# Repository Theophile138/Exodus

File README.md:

# Exodus

## Documentation

[Documentation du code](./Software/Doc)

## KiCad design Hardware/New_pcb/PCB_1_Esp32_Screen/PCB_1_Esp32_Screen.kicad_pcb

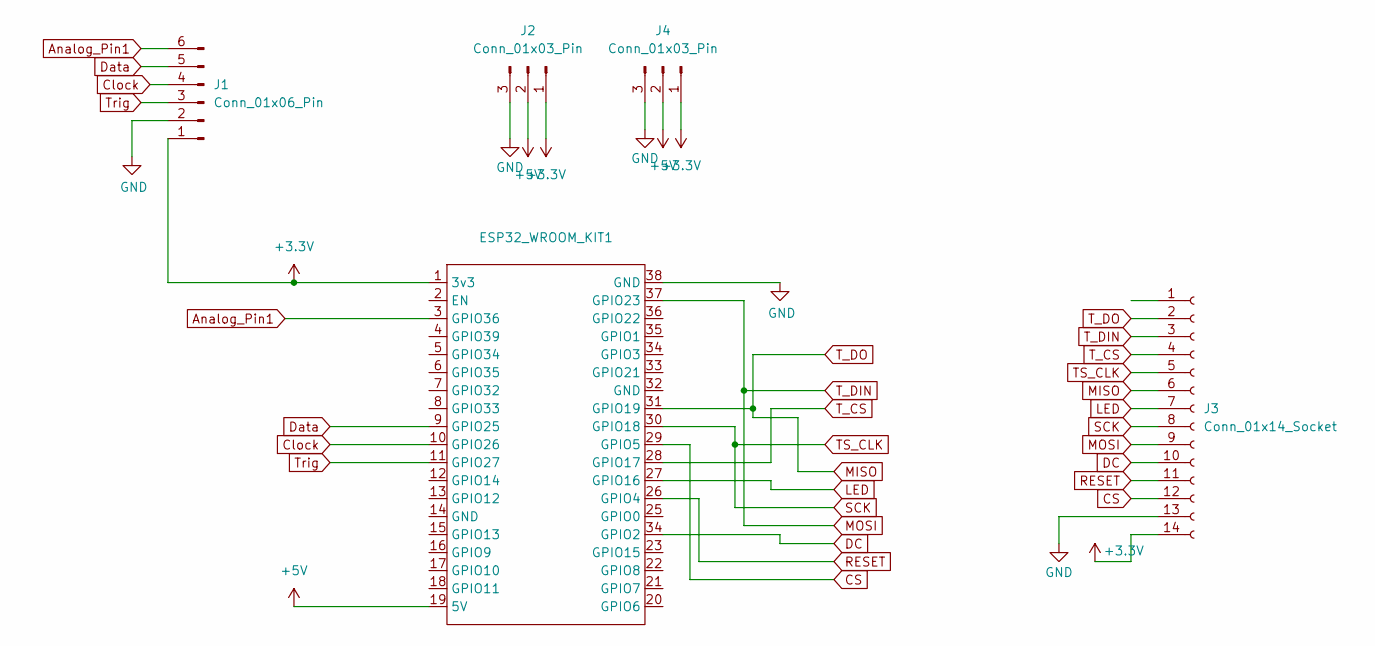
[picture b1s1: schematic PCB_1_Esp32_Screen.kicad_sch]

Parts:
ESP32_WROOM_KIT1: Esp32_Wroom32_DevKit
J1: Conn_01x06_Pin; PinHeader_1x06_P2.54mm_Vertical
J2, J4: Conn_01x03_Pin; PinHeader_1x03_P2.54mm_Vertical
J3: Conn_01x14_Socket; PinSocket_1x14_P2.54mm_Vertical

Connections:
+3.3V: ESP32_WROOM_KIT1.1 (3v3), J1.1, J2.1, J3.14, J4.1
+5V: ESP32_WROOM_KIT1.19 (5V), J2.2, J4.2
Analog_Pin1: ESP32_WROOM_KIT1.3 (GPIO36), J1.6
CS: ESP32_WROOM_KIT1.29 (GPIO5), J3.12
Clock: ESP32_WROOM_KIT1.10 (GPIO26), J1.4
DC: ESP32_WROOM_KIT1.34 (GPIO2), J3.10
Data: ESP32_WROOM_KIT1.9 (GPIO25), J1.5
GND: ESP32_WROOM_KIT1.38 (GND), J1.2, J2.3, J3.13, J4.3
LED: ESP32_WROOM_KIT1.27 (GPIO16), J3.7
MISO: ESP32_WROOM_KIT1.31 (GPIO19), J3.2, J3.6
MOSI: ESP32_WROOM_KIT1.37 (GPIO23), J3.3, J3.9
RESET: ESP32_WROOM_KIT1.26 (GPIO4), J3.11
SCK: ESP32_WROOM_KIT1.30 (GPIO18), J3.5, J3.8
T_CS: ESP32_WROOM_KIT1.28 (GPIO17), J3.4
Trig: ESP32_WROOM_KIT1.11 (GPIO27), J1.3

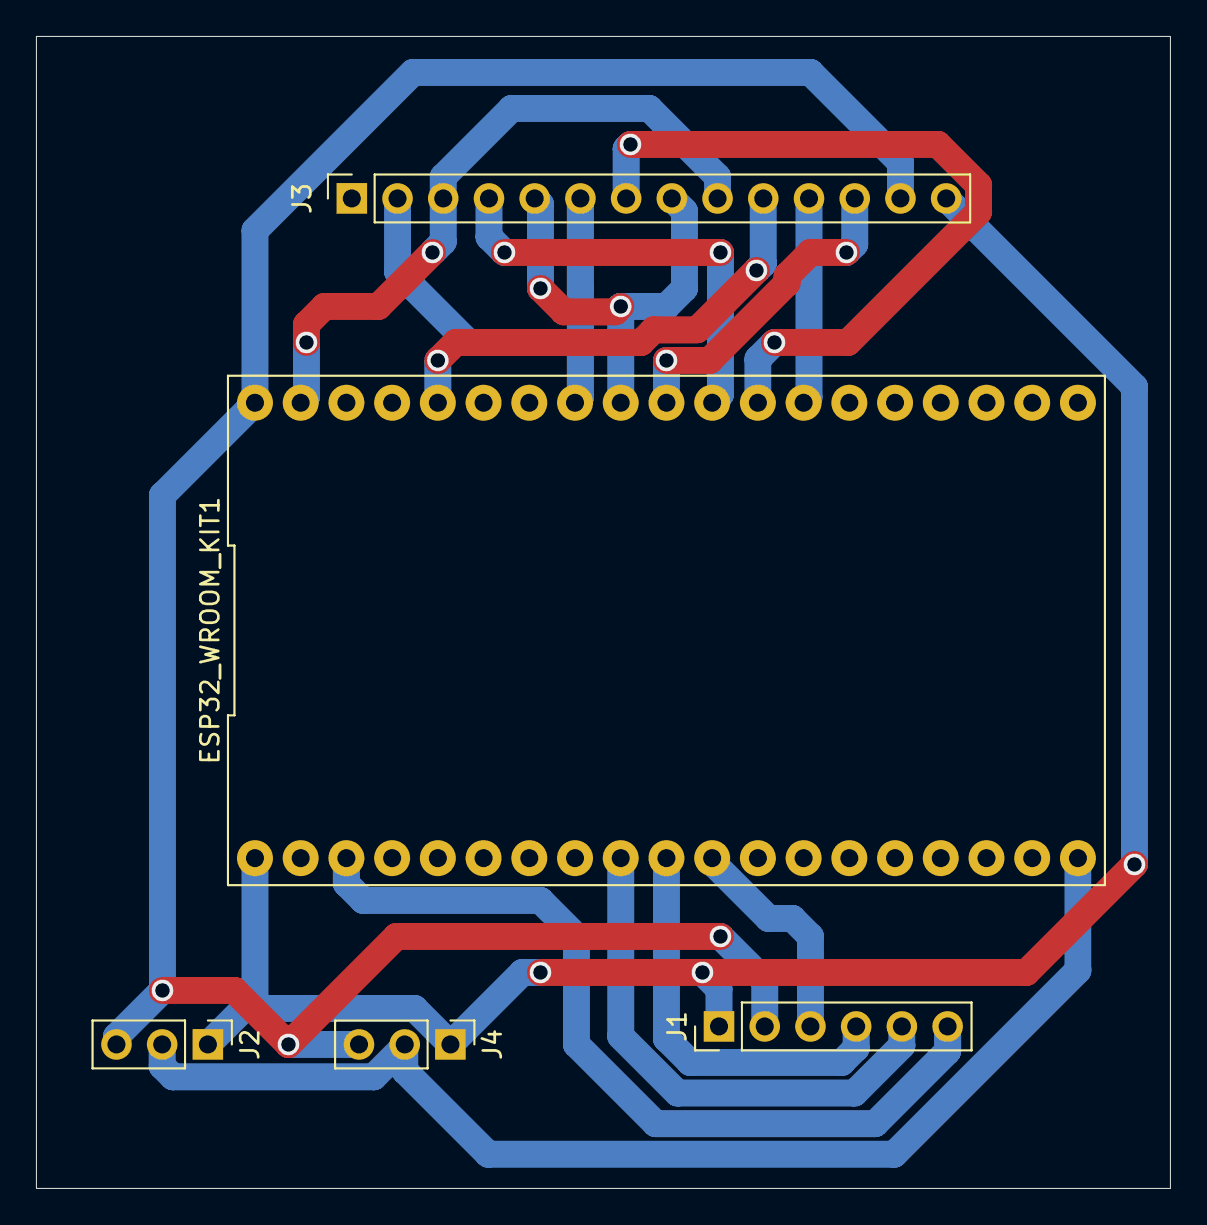
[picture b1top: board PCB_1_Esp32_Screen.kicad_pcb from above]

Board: 2 copper layers, 63.0 x 64.0 mm, 5 parts (0 on the bottom side), 15 nets.

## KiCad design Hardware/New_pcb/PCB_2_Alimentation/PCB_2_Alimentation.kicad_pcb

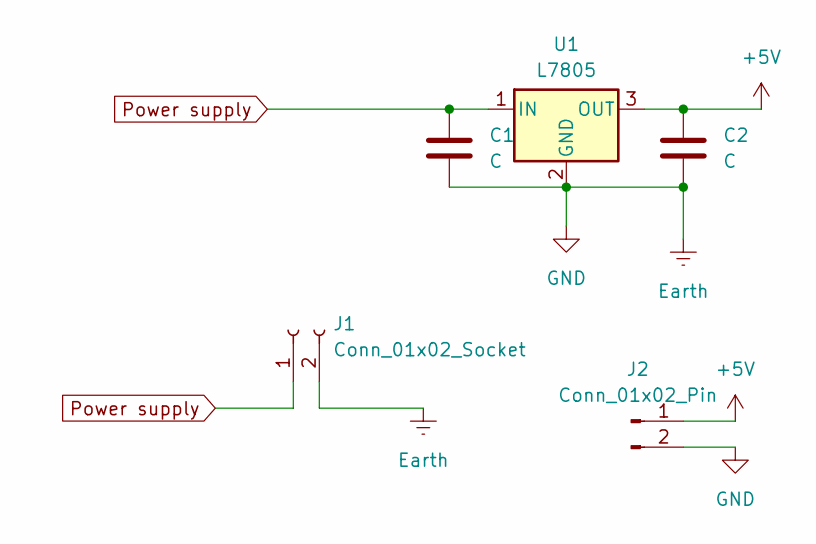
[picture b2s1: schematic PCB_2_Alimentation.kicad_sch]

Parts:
C1, C2: C; CP_Radial_D4.0mm_P1.50mm
J1: Conn_01x02_Socket; TerminalBlock_bornier-2_P5.08mm
J2: Conn_01x02_Pin; PinHeader_1x02_P2.54mm_Horizontal
U1: L7805; TO-220-3_Vertical

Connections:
+5V: C2.1, J2.1, U1.3 (OUT)
Earth: C1.2, C2.2, J1.2, J2.2, U1.2 (GND)
Power supply: C1.1, J1.1, U1.1 (IN)

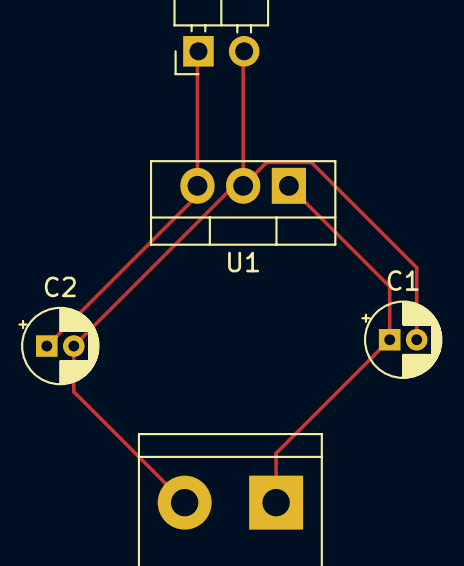
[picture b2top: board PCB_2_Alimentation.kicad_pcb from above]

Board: 2 copper layers, 5 parts (0 on the bottom side), 3 nets.

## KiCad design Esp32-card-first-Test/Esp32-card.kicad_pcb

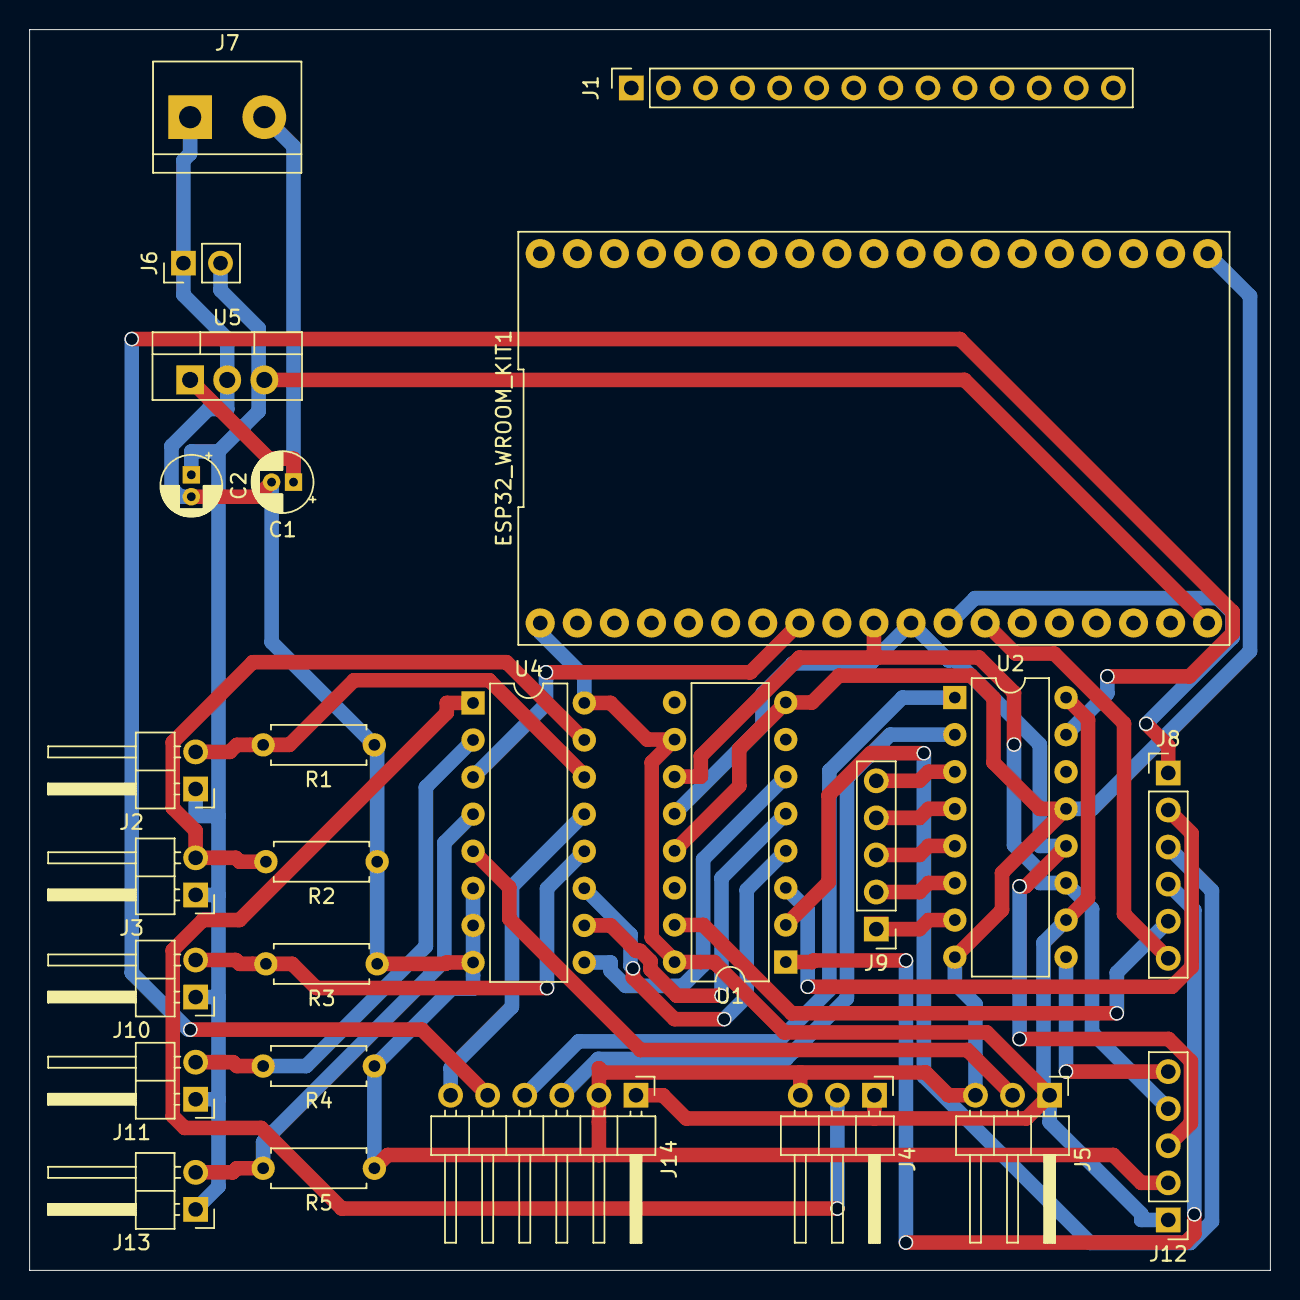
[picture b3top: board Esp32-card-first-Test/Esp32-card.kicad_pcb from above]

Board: 2 copper layers, 85.0 x 85.0 mm, 26 parts (0 on the bottom side), 35 nets.

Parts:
C1, C2: C; CP_Radial_D4.0mm_P1.50mm
ESP32_WROOM_KIT1: Esp32_Wroom32_DevKit
J1: Conn_01x14_Socket; PinSocket_1x14_P2.54mm_Vertical
J2, J3, J10, J11, J13: Conn_01x02_Pin; PinHeader_1x02_P2.54mm_Horizontal
J4, J5: Conn_01x03_Pin; PinHeader_1x03_P2.54mm_Horizontal
J6: Conn_01x02_Pin; PinHeader_1x02_P2.54mm_Vertical
J7: Conn_01x02_Socket; TerminalBlock_bornier-2_P5.08mm
J8: Conn_01x06_Pin; PinHeader_1x06_P2.54mm_Vertical
J9, J12: Conn_01x05_Pin; PinHeader_1x05_P2.54mm_Vertical
J14: Conn_01x06_Pin; PinHeader_1x06_P2.54mm_Horizontal
R1, R2, R3, R4, R5: R; R_Axial_DIN0207_L6.3mm_D2.5mm_P7.62mm_Horizontal
U1, U2: 74HC595; DIP-16_W7.62mm
U4: 74HC4051; DIP-16_W7.62mm
U5: L7805; TO-220-3_Vertical

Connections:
3v3: ESP32_WROOM_KIT1.1 (3v3), J4.1, J5.1, J12.1, J14.1, U1.10 (~SRCLR), U1.16 (VCC), U2.10 (~SRCLR), U2.16 (VCC), U4.16 (VCC)
5v: C2.1, ESP32_WROOM_KIT1.19 (5V), J2.1, J3.1, J6.2, J10.1, J11.1, J13.1, U5.3 (OUT)
Analog_Pin1: ESP32_WROOM_KIT1.8 (GPIO33), U4.3 (A)
Capteur_Autre_1: J11.2, R4.2, U4.2 (A6)
Capteur_Autre_2: J13.2, R5.2, U4.4 (A7)
Capteur_Force_1: J2.2, R1.2, U4.14 (A1)
Capteur_Force_2: J3.2, R2.2, U4.15 (A2)
Capteur_Force_3: J10.2, R3.2, U4.12 (A3)
Capteur_Hall_1: J4.2, U4.1 (A4)
Capteur_Hall_2: J5.2, U4.5 (A5)
Clock: ESP32_WROOM_KIT1.10 (GPIO26), J12.4, U1.11 (SRCLK), U2.11 (SRCLK)
Data: ESP32_WROOM_KIT1.9 (GPIO25), U1.14 (SER)
GND: C1.2, C2.2, ESP32_WROOM_KIT1.20 (GND), J4.3, J5.3, J6.1, J7.1, J12.2, J14.2, R1.1, R2.1, R3.1, R4.1, R5.1, U1.8 (GND), U1.13 (~OE), U2.8 (GND), U2.13 (~OE), U4.6 (~E), U4.7 (VEE), U4.8 (GND), U5.2 (GND)
M1_Pin_Dir1: J8.5, U1.15 (QA)
M1_Pin_Dir2: J8.4, U1.1 (QB)
M1_Pin_EN: ESP32_WROOM_KIT1.13 (GPIO12), J8.6
M2_Pin_Dir1: J8.3, U1.2 (QC)
M2_Pin_Dir2: J8.2, U1.3 (QD)
M2_Pin_EN: ESP32_WROOM_KIT1.12 (GPIO14), J8.1
unnamed: J9.1, U2.7 (QH)
unnamed: J9.2, U2.6 (QG)
unnamed: J9.3, U2.5 (QF)
unnamed: J9.4, U2.4 (QE)
unnamed: J9.5, U2.3 (QD)
unnamed: J12.5, U2.9 (QH')
unnamed: J14.3, U2.2 (QC)
unnamed: J14.4, U2.1 (QB)
unnamed: J14.5, U2.15 (QA)
unnamed: J14.6, U4.13 (A0)
unnamed: U1.4 (QE), U4.11 (S0)
unnamed: U1.5 (QF), U4.10 (S1)
unnamed: U1.6 (QG), U4.9 (S2)
unnamed: U1.9 (QH'), U2.14 (SER)
Power supply: C1.1, J7.2, U5.1 (IN)
Trig: ESP32_WROOM_KIT1.11 (GPIO27), J12.3, U1.12 (RCLK), U2.12 (RCLK)

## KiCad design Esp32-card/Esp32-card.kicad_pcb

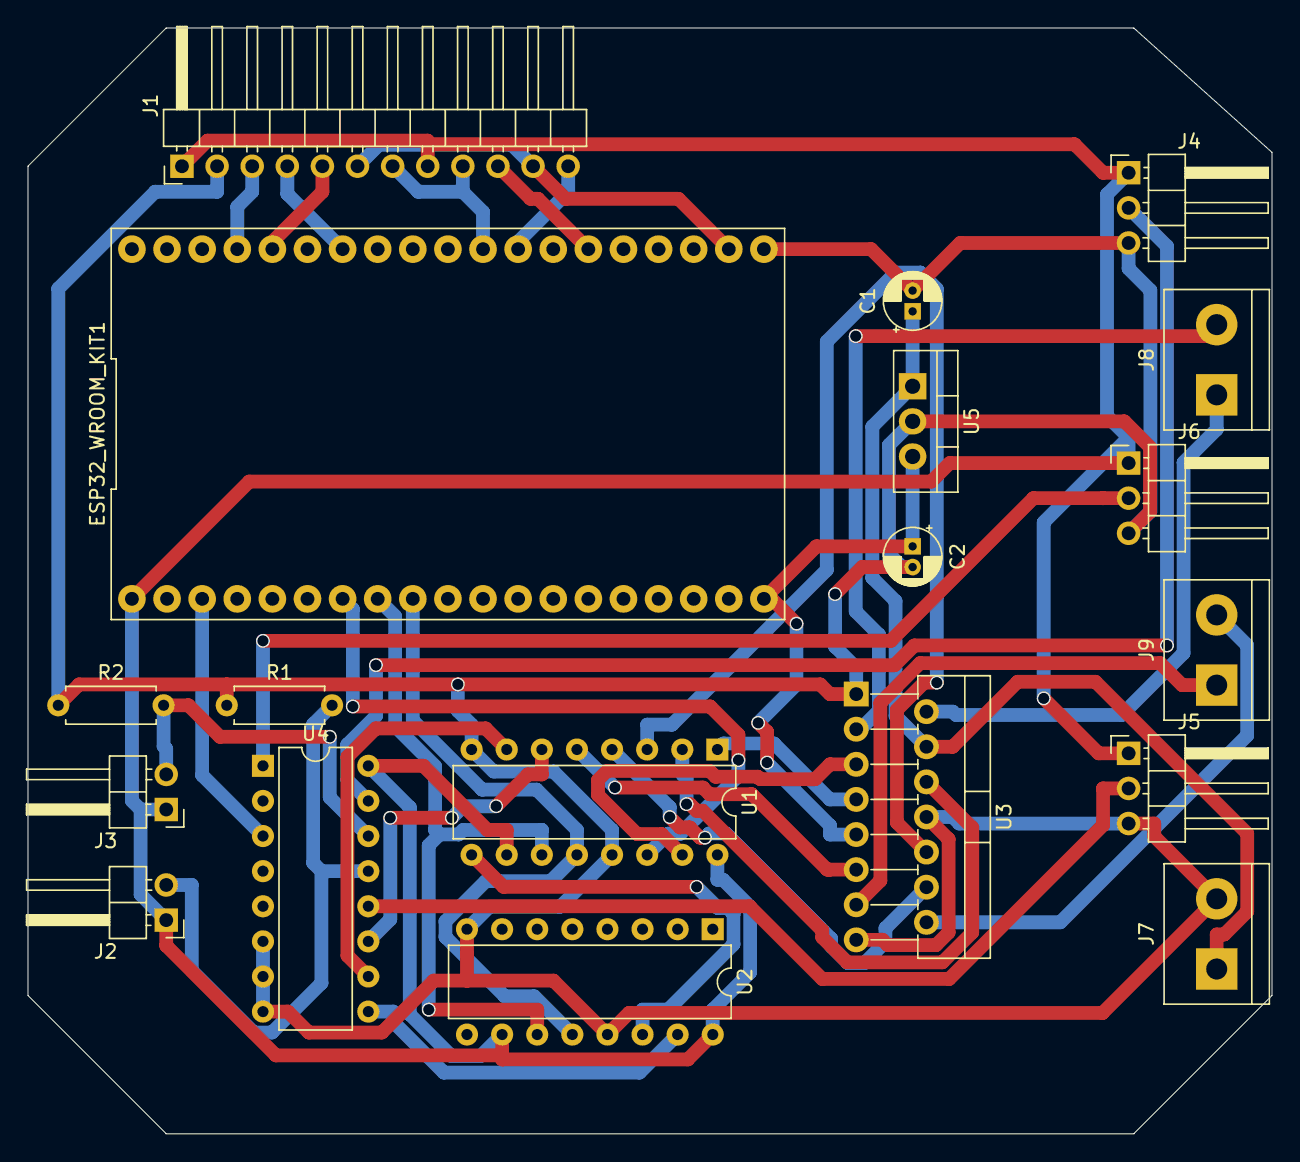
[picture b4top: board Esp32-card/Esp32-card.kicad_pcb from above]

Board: 2 copper layers, 90.0 x 80.0 mm, 19 parts (0 on the bottom side), 34 nets.

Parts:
C1, C2: C; CP_Radial_D4.0mm_P1.50mm
ESP32_WROOM_KIT1: Esp32_Wroom32_DevKit
J1: Conn_01x12_Pin; PinHeader_1x12_P2.54mm_Horizontal
J2, J3: Conn_01x02_Pin; PinHeader_1x02_P2.54mm_Horizontal
J4, J5, J6: Conn_01x03_Pin; PinHeader_1x03_P2.54mm_Horizontal
J7, J8, J9: Conn_01x02_Socket; TerminalBlock_bornier-2_P5.08mm
R1, R2: R; R_Axial_DIN0207_L6.3mm_D2.5mm_P7.62mm_Horizontal
U1, U2: 74HC595; DIP-16_W7.62mm
U3: L298N; TO-220-15_P2.54x2.54mm_StaggerOdd_Lead4.58mm_Vertical
U4: 74HC4051; DIP-16_W7.62mm
U5: L7805; TO-220-3_Vertical

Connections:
3v3: ESP32_WROOM_KIT1.1 (3v3), J1.1, J1.8, J2.1, J3.1, J4.1, J5.1, J6.1, U1.10 (~SRCLR), U1.16 (VCC), U2.10 (~SRCLR), U2.16 (VCC), U4.16 (VCC)
5v: C2.1, ESP32_WROOM_KIT1.19 (5V), U3.9 (Vss), U5.3 (OUT)
Analog_Pin1: ESP32_WROOM_KIT1.3 (GPIO36), U4.3 (A)
Capteur_Flexion_1: J2.2, R1.2, U4.13 (A0)
Capteur_Flexion_2: J3.2, R2.2, U4.14 (A1)
Capteur_Hall_1: J4.2, U4.15 (A2)
Capteur_Hall_2: J5.2, U4.12 (A3)
Capteur_Hall_3: J6.2, U4.1 (A4)
Clock: ESP32_WROOM_KIT1.8 (GPIO33), U1.11 (SRCLK), U2.11 (SRCLK)
Data: ESP32_WROOM_KIT1.7 (GPIO32), U1.14 (SER)
GND: C1.2, C2.2, ESP32_WROOM_KIT1.20 (GND), J1.2, J4.3, J5.3, J6.3, J7.2, R1.1, R2.1, U1.8 (GND), U1.13 (~OE), U2.8 (GND), U2.13 (~OE), U3.1 (SENSE_A), U3.8 (GND), U3.15 (SENSE_B), U4.6 (~E), U4.7 (VEE), U4.8 (GND), U5.2 (GND)
M1_Pin_Dir1: U1.15 (QA), U3.5 (IN1)
M1_Pin_Dir2: U1.1 (QB), U3.7 (IN2)
M1_Pin_EN: U1.2 (QC), U3.6 (EnA)
M2_Pin_Dir1: U1.3 (QD), U3.10 (IN3)
M2_Pin_Dir2: U1.4 (QE), U3.12 (IN4)
M2_Pin_EN: U1.5 (QF), U3.11 (EnB)
unnamed: ESP32_WROOM_KIT1.34 (GPIO2), J1.5
unnamed: ESP32_WROOM_KIT1.32 (GPIO4), J1.4
unnamed: ESP32_WROOM_KIT1.35 (GPIO15), J1.3
unnamed: ESP32_WROOM_KIT1.28 (GPIO18), J1.7, J1.9
unnamed: ESP32_WROOM_KIT1.27 (GPIO19), J1.12
unnamed: ESP32_WROOM_KIT1.25 (GPIO21), J1.10
unnamed: ESP32_WROOM_KIT1.21 (GPIO23), J1.6, J1.11
unnamed: J8.1, U3.2 (OUT1)
unnamed: J8.2, U3.3 (OUT2)
unnamed: J9.1, U3.13 (OUT3)
unnamed: J9.2, U3.14 (OUT4)
unnamed: U1.6 (QG), U4.11 (S0)
unnamed: U1.9 (QH'), U2.14 (SER)
unnamed: U1.7 (QH), U4.10 (S1)
unnamed: U2.15 (QA), U4.9 (S2)
Power supply: C1.1, J7.1, U3.4 (Vs), U5.1 (IN)
Trig: ESP32_WROOM_KIT1.9 (GPIO25), U1.12 (RCLK), U2.12 (RCLK)

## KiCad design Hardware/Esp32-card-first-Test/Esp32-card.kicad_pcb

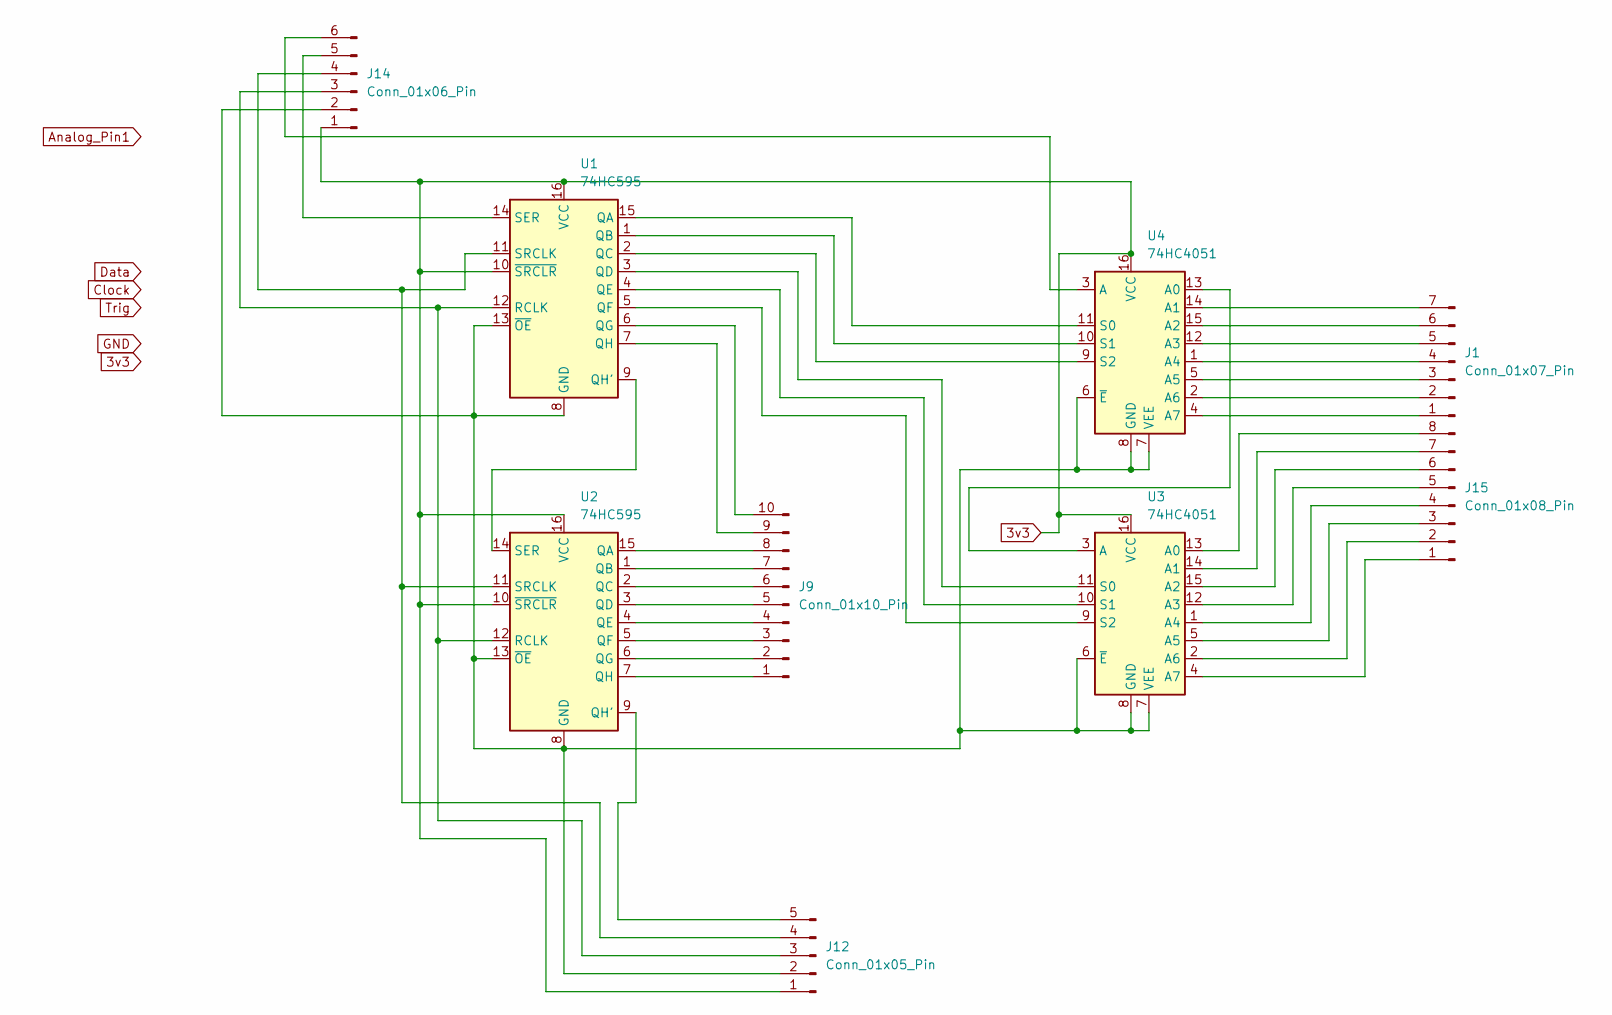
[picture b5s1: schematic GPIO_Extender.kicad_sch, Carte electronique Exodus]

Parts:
J1: Conn_01x07_Pin; PinHeader_1x07_P2.54mm_Vertical
J9: Conn_01x10_Pin; PinHeader_1x10_P2.54mm_Vertical
J12: Conn_01x05_Pin; PinHeader_1x05_P2.54mm_Vertical
J14: Conn_01x06_Pin; PinHeader_1x06_P2.54mm_Vertical
J15: Conn_01x08_Pin; PinHeader_1x08_P2.54mm_Vertical
U1, U2: 74HC595; DIP-16_W7.62mm
U3, U4: 74HC4051; DIP-16_W7.62mm

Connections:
3v3: J12.1, J14.1, U1.10 (~SRCLR), U1.16 (VCC), U2.10 (~SRCLR), U2.16 (VCC), U3.16 (VCC), U4.16 (VCC)
unnamed: J1.1, U4.4 (A7)
unnamed: J1.2, U4.2 (A6)
unnamed: J1.3, U4.5 (A5)
unnamed: J1.4, U4.1 (A4)
unnamed: J1.5, U4.12 (A3)
unnamed: J1.6, U4.15 (A2)
unnamed: J1.7, U4.14 (A1)
unnamed: J9.1, U2.7 (QH)
unnamed: J9.2, U2.6 (QG)
unnamed: J9.3, U2.5 (QF)
unnamed: J9.4, U2.4 (QE)
unnamed: J9.5, U2.3 (QD)
unnamed: J9.6, U2.2 (QC)
unnamed: J9.7, U2.1 (QB)
unnamed: J9.8, U2.15 (QA)
unnamed: J9.9, U1.7 (QH)
unnamed: J9.10, U1.6 (QG)
unnamed: J12.2, J14.2, U1.8 (GND), U1.13 (~OE), U2.8 (GND), U2.13 (~OE), U3.6 (~E), U3.7 (VEE), U3.8 (GND), U4.6 (~E), U4.7 (VEE), U4.8 (GND)
unnamed: J12.3, J14.3, U1.12 (RCLK), U2.12 (RCLK)
unnamed: J12.4, J14.4, U1.11 (SRCLK), U2.11 (SRCLK)
unnamed: J12.5, U2.9 (QH')
unnamed: J14.5, U1.14 (SER)
unnamed: J14.6, U4.3 (A)
unnamed: J15.1, U3.4 (A7)
unnamed: J15.2, U3.2 (A6)
unnamed: J15.3, U3.5 (A5)
unnamed: J15.4, U3.1 (A4)
unnamed: J15.5, U3.12 (A3)
unnamed: J15.6, U3.15 (A2)
unnamed: J15.7, U3.14 (A1)
unnamed: J15.8, U3.13 (A0)
unnamed: U1.15 (QA), U4.11 (S0)
unnamed: U1.1 (QB), U4.10 (S1)
unnamed: U1.2 (QC), U4.9 (S2)
unnamed: U1.3 (QD), U3.11 (S0)
unnamed: U1.4 (QE), U3.10 (S1)
unnamed: U1.5 (QF), U3.9 (S2)
unnamed: U1.9 (QH'), U2.14 (SER)
unnamed: U3.3 (A), U4.13 (A0)

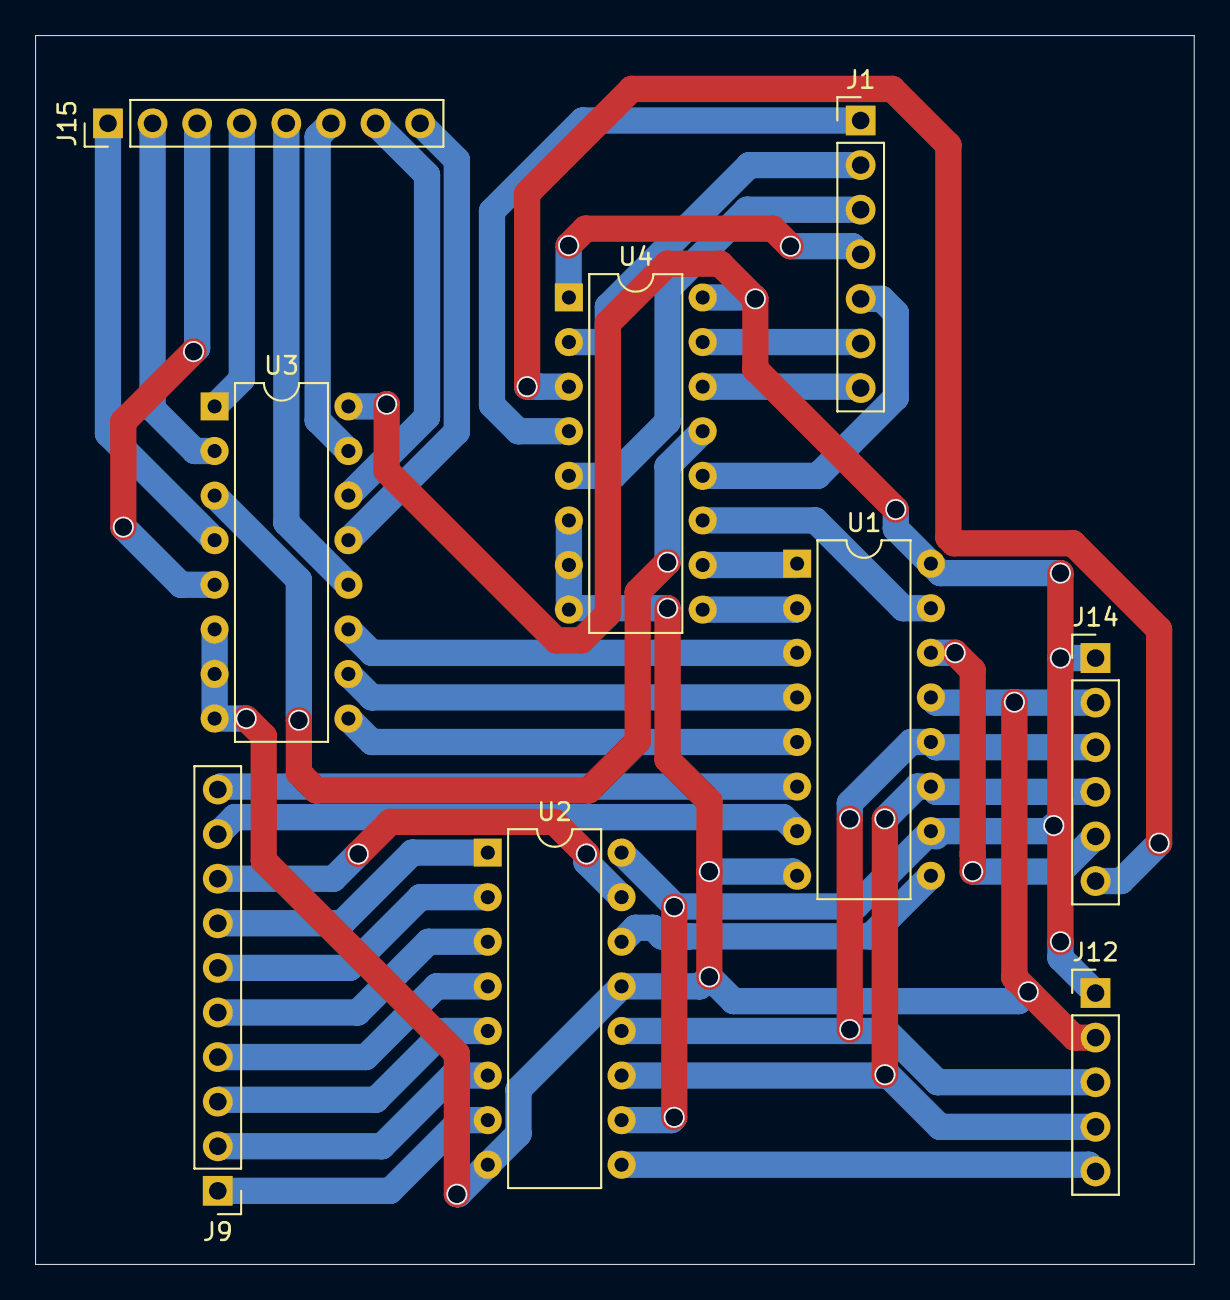
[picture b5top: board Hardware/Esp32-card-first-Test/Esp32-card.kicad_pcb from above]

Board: 2 copper layers, 66.0 x 70.0 mm, 9 parts (0 on the bottom side), 40 nets.

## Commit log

2024-12-02 Kicad setup
2024-12-02 Library esp32
2024-12-03 Schema du registre a decalage et du multiplexeur
2024-12-08 Esp32 Lib avec fichier 3d
2024-12-09 Alimentation
2025-01-26 Add software
2025-01-27 New cart and new config
2025-01-27 Software config
2025-01-30 Add in the config capteurDeforce
2025-02-15 add and congif Visual studio code projet
2025-02-15 add documentation
2025-02-15 baudrate
2025-02-15 draw picture
2025-02-16 python converter , esp start img , class gauge
2025-02-18 add a selection menu
2025-02-21 lib pour les boutons avec callback
2025-02-23 manage task time and real value meter
2025-02-23 Gauge exemple
2025-02-23 Reorganisation
2025-02-24 selction entre une vrai config et un exemple
2025-02-25 Add files via upload
    MAJ du pdf
2025-02-25 set pin
2025-02-25 test
2025-02-25 LibDriver modification
2025-03-04 Create PCB_Scinde
2025-03-24 pcb amelioration
2025-03-25 Capteur accelerometre
2025-03-29 multiplex
2025-04-11 lib servo + simulateur cpp + code ino de test dans task 2
2025-05-15 Ajout de documentation
2025-05-15 Nom Logos
2025-05-15 Readme
2025-05-15 Images ReadMe
2025-05-15 Images pour de bon cette fois promis
2025-05-15 test images
2025-05-15 Accès facile à la doc
2025-05-20 Enfilage du bras
2025-05-25 aled
2025-05-26 Activer/Desactiver bras
2025-05-26 Ajout d'images du bras
2025-05-26 Enlève crash
2025-05-26 Test Images Bras
2025-05-26 Resize Images
2025-05-26 Bouton Activation Bras
2025-05-27 pablo stop
2025-05-27 pablo
